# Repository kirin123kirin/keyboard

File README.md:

# 自作キーボードの沼

## 以下の要件を満たす分割キーボードがないから作りたい。

* 癖のない一般的なキーピッチ、配列である
* 日本語配列である
* 光らなくてよい
* 一般的なテンキーレスを普通に左右に分割しただけで特殊な配列ではないこと
* 「6」、「Y」、「B」は右手で押す
* IME切り替えはトグルではなくMacのように「英数」、「かな」で独立したキー切替をする
* USB Type-C
* 左右どちら側のUSBに接続しても使える
* キーキャップにかな表記はいらない
* キーキャップに英語配列時の記号も小さく表記したい
* Thinkpad トラックポイントを右手側につけたい

## 沼１：レイアウト
1. [レイアウトを考える](http://www.keyboard-layout-editor.com/)

## 沼２：回路基盤設計
2. [回路図の書き方](https://www.youtube.com/watch?v=dNfaLM5PUVM&list=PLKe0_8RR2yrSu2fZAs2D8_bfYQ3JGBO-w)
3. [自動レイアウト](https://github.com/yskoht/keyboard-layouter)
4. [自動配線](https://freerouting.mihosoft.eu/)
5. [Elecrow発注データ作成は自作](https://github.com/kirin123kirin/keyboard/blob/main/pcb/basic_L/garbar.py)

## 沼３：ファームウェア書き込み
6. [半自動firmware作成](https://kbfirmware.com/)
   -> Or import from keyboard-layout-editor.comの下のテキストボックスにKyeboard Layout Editorのraw dataの内容をコピペ

## 沼４：スイッチ選び
7. 赤軸(軽い) or 黒軸(重い) / CherryMX(90円) or KailhBox(40円)

## 沼５：キーキャップ選び
8. [Filco交換用](https://amzn.to/37BaPCG)

9. [刻印サービス](https://yushakobo.jp/keycap-laser-marking/)
  -> 高いのでやめる

## 沼６：ケース作成
10. [Plate & Case Builder](http://builder.swillkb.com/)
  -> keyboard-layout-editorのRAWデータからCADデータ自動作成

11. [Kicad PCB to Fusion360](https://garchiving.com/output-3d-model-with-kicad/)

12. [Elecrow 3D Printing Service](https://www.elecrow.com/3d-printing-service.html)

## 沼７：トラックポイントをつける
TODO

## かかった費用

| カテゴリー     	| 購入製品                                                      	| 個数  	| 単価    	| 小計(円)  	| 購入店                	|
| :---------------- | :---------------------------------------------------------------  | -------:  | --------: | --------: | :-----------------------  |
| マイコンボード 	| [Elite-C](https://yushakobo.jp/shop/elite-c/)                   	| 2     	| 2805    	| 5610     	| [遊舎工房](https://yushakobo.jp/shop/elite-c/)              	|
| マイコンボードソケット化 	| [ピンヘッダー ストリップ ピンソケット 40ピン](https://amzn.to/2Ml5kjq)                   	| 1     	| 720    	| 720     	| [Amazon](https://amzn.to/2Ml5kjq)              	|
| PCB基盤        	| 左                                                            	| 104.1 	| $27.35  	| 2,847 	| ElecrowPCB            	|
| PCB基盤        	| 右                                                            	| 104.1 	| $36.37  	| 3,786 	| ElecrowPCB            	|
| PCB基盤        	| 送料                                                          	| 104.1 	| $20.12  	| 2,094 	| ElecrowPCB            	|
| ケース         	| 左右光造形                                                      	| 104.1 	| $70     	| 7,287   	| Elecrow3DPrintService 	|
| ケース         	| トッププレート                                                	| 104.1 	| $20     	| 2,082   	| Elecrow3DPrintService 	|
| ケース         	| 送料                                                          	| 104.1 	| $14     	| 1,447  	| Elecrow3DPrintService 	|
| キースイッチ   	| [Kailh Box黒軸](https://amzn.to/3h1IFUD)                                                 	| 104.1 	| $34     	| 3508.17  	| Aliexpress            	|
| スタビライザー 	| [ブラックチェリースタビライザー](https://ja.aliexpress.com/item/32831318362.html?spm=a2g0s.9042311.0.0.46c54c4d9BF958)                                                           	| 104.1 	| $5.90   	| 614.19   	| Aliexpress            	|
| キーキャップ   	| [Majestouch 交換用キーキャップセット 日本語108キー・かななし](https://amzn.to/37BaPCG) 	| 1     	| 3420    	| 3420     	| [Amazon](https://amzn.to/37BaPCG)	|
| 配線類         	| [ダイオード500個](https://amzn.to/2Wz1wNc)                                               	| 1     	| 1082    	| 1082     	| [Amazon](https://amzn.to/2Wz1wNc)                	|
| 配線類         	| [抵抗セット](https://amzn.to/3nESg6m)                                                    	| 1     	| 890     	| 890      	| [Amazon](https://amzn.to/3nESg6m)                	|
| 配線類         	| [はんだ線](https://amzn.to/3mBjyJs)、[フラックス](https://amzn.to/3p1iNLk)                                          	| 1     	| 916     	| 916      	| [Amazon](https://amzn.to/3p1iNLk)                	|
| TRRS           	| [３．５ｍｍ４極ミニジャック　基板取付用　ＭＪ－４ＰＰ－９](https://akizukidenshi.com/catalog/g/gC-06070/)      	| 2     	| 55      	| 110      	| 秋月通商              	|
| デバック用     	| [ブレッドボード5個セット](https://amzn.to/3nD7uZn)                                       	| 1     	| 750     	| 750      	| [Amazon](https://amzn.to/3nD7uZn)                	|
| デバック用     	| [マスキングテープ3個](https://amzn.to/2J5NEa9)                                           	| 1     	| 498     	| 498      	| [Amazon](https://amzn.to/2J5NEa9)                	|
| デバック用     	| ジャンパー線、[タクトスイッチ10個](https://amzn.to/3mDJrrU)                              	| 1     	| 660     	| 660      	| 秋月通商,[Amazon](https://amzn.to/3mDJrrU)              	|
| 工具           	| [はんだキット](https://amzn.to/2WwUdWA)                                                  	| 1     	| 3599    	| 3599     	| [Amazon](https://amzn.to/2WwUdWA)                	|
| 工具           	| [ノギス](https://amzn.to/3mIHx9L)                                	| 1     	| 799    	| 799     	| [Amazon](https://amzn.to/3mIHx9L)	|
| レイアウト設計        	| [キーボードレイアウト設計](http://www.keyboard-layout-editor.com/)                                                         	| 1     	| 0       	| 0        	| OSS             	|
| PCB設計        	| [Kicad](https://kicad.org/)                                                         	| 1     	| 0       	| 0        	| OSS             	|
| PCB設計        	| [基盤自動レイアウトプラグイン](https://github.com/yskoht/keyboard-layouter)                                                         	| 1     	| 0       	| 0        	| OSS             	|
| PCB設計        	| [freerouting(基盤自動配線)](https://github.com/freerouting/freerouting)                                                         	| 1     	| 0       	| 0        	| OSS             	|
| ケース、トッププレート設計     	| [Fusion360個人利用](https://www.autodesk.co.jp/products/fusion-360/overview)                                                 	| 1     	| 0       	| 0        	| Adobe                 	|
| Firmware       	| [qmk_firmware](https://github.com/qmk/qmk_firmware)                                                  	| 1     	| 0       	| 0        	| Github                	|
| Firmware       	| [Keyboard Firmware Builder](https://kbfirmware.com/)                                                         	| 1     	| 0       	| 0        	| OSS             	|
| Firmwareビルド用 	| [Ubuntu18.04LTS Server](http://ftp.riken.jp/Linux/ubuntu-releases/18.04/)                                                	| 1     	| 0       	| 0        	| Ubuntu                	|
| Firmwareソース編集用	| [Visual Studio2019Comunity](https://visualstudio.microsoft.com/ja/downloads/)                                   	| 1     	| 0       	| 0        	| MicroSoft             	|
|                	|                                                               	|       	| 合計    	| 42,334円	|

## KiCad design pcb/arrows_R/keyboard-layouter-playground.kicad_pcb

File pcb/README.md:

** qmk data version rev1 later **

# 自作基盤設計データ
## Lisense
This software is released under the [Creative Commons CC-BY-SA 4.0 License](https://creativecommons.org/licenses/by-sa/4.0/legalcode), see LICENSE.

## [Powerd by Kicad](https://kicad.org/)

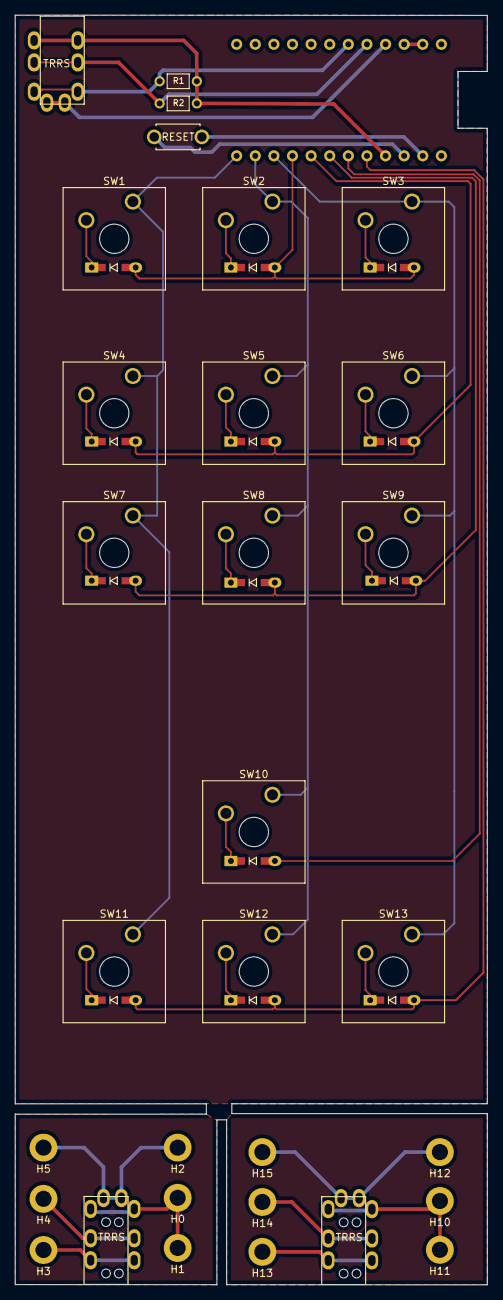
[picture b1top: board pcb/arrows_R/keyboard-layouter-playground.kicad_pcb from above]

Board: 2 copper layers, 64.4 x 173.3 mm, 45 parts (1 on the bottom side), 36 nets.

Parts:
D1, D2, D3, D4, D5, D6, D7, D8, D9, D10, D11, D12, D13: DIODE; D3_TH
H0, H10: MIC-Left; MountingHole_2.2mm_M2_ISO14580_Pad
H1, H11: MIC-Right; MountingHole_2.2mm_M2_ISO14580_Pad
H2, H5, H12, H15: GND; MountingHole_2.2mm_M2_ISO14580_Pad
H3, H13: Left; MountingHole_2.2mm_M2_ISO14580_Pad
H4, H14: Right; MountingHole_2.2mm_M2_ISO14580_Pad
J1, J2, J3: MJ-4PP-9
R1, R2: 4.7k; R
SW1, SW2, SW3, SW4, SW5, SW6, SW7, SW8, SW9, SW10, SW11, SW12, SW13: SW_Push; SW_Cherry_MX_1.00u_Plate
SW_RST2: SW_PUSH; ResetSW
U1: ProMicro; ProMicro_v3.5

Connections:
COL1: SW1.1, SW4.1, SW7.1, SW11.1, U1.13
COL2: SW2.1, SW5.1, SW8.1, SW10.1, SW12.1, U1.14
COL3: SW3.1, SW6.1, SW9.1, SW13.1, U1.15
unnamed: D1.1, SW1.2
unnamed: D2.1, SW2.2
unnamed: D3.1, SW3.2
unnamed: D4.1, SW4.2
unnamed: D5.1, SW5.2
unnamed: D6.1, SW6.2
unnamed: D7.1, SW7.2
unnamed: D8.1, SW8.2
unnamed: D9.1, SW9.2
unnamed: D10.1, SW10.2
unnamed: D11.1, SW11.2
unnamed: D12.1, SW12.2
unnamed: D13.1, SW13.2
unnamed: H0.1, H1.1, J1.D
unnamed: H2.1, H5.1, J1.A
unnamed: H3.1, J1.B
unnamed: H4.1, J1.C
unnamed: H10.1, H11.1, J3.D
unnamed: H12.1, H15.1, J3.A
unnamed: H13.1, J3.B
unnamed: H14.1, J3.C
unnamed: J2.A, U1.4
unnamed: J2.B, R1.2, R2.2, U1.21
unnamed: J2.D, R1.1, U1.6
unnamed: SW_RST2.1, U1.22
unnamed: SW_RST2.2, U1.23
unnamed: U1.2, U1.3
SDA2: J2.C, R2.1, U1.5
row1: D1.2, D2.2, D3.2, U1.16
row2: D4.2, D5.2, D6.2, U1.17
row3: D7.2, D8.2, D9.2, U1.18
row4: D10.2, U1.19
row5: D11.2, D12.2, D13.2, U1.20

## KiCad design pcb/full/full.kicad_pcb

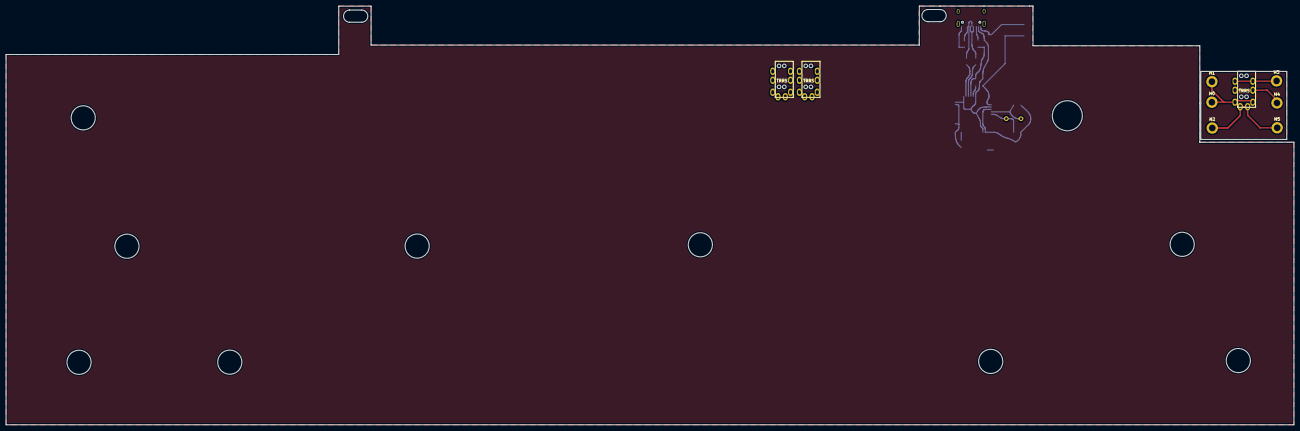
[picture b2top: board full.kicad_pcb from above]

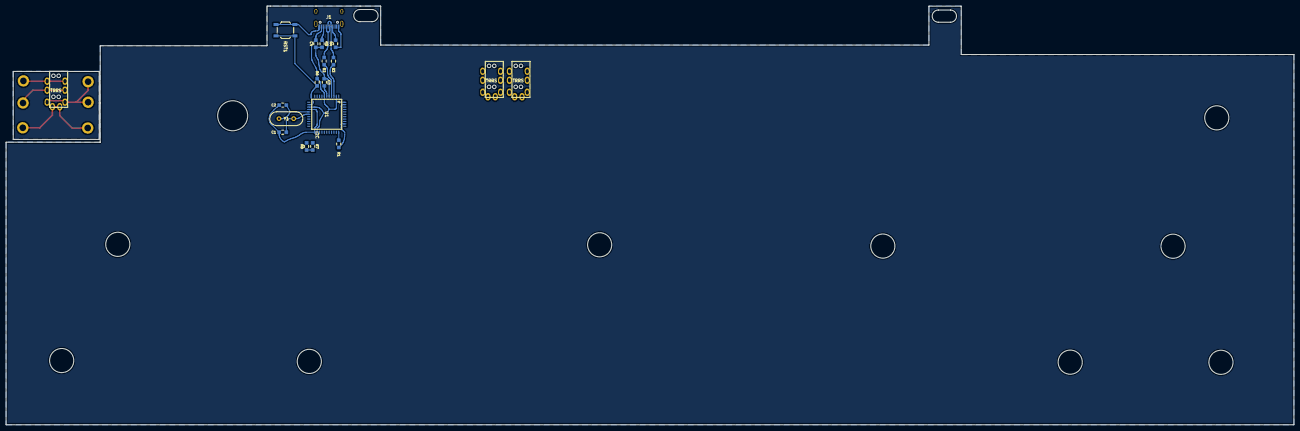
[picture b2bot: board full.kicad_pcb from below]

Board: 2 copper layers, 429.5 x 139.6 mm, 25 parts (15 on the bottom side), 15 nets.

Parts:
C1, C2: 22p; 2012M
C3, C4: 1u; 2012M
H0: MIC-Left; MountingHole_2.2mm_M2_ISO14580_Pad
H1: MIC-Right; MountingHole_2.2mm_M2_ISO14580_Pad
H2, H5: GND; MountingHole_2.2mm_M2_ISO14580_Pad
H3: Left; MountingHole_2.2mm_M2_ISO14580_Pad
H4: Right; MountingHole_2.2mm_M2_ISO14580_Pad
J1: MJ-4PP-9
J1#2: TYPE-C-31-M-12
J2, J3: AudioJack4; MJ-4PP-9
R1, R6: 10k; 2012M
R2, R3: 22; 2012M
R4, R5, R7, R8: 5.1k; 2012M
RST1: SW_Push; SW_SPST_TL3342
U1: ATmega32U4-AU; TQFP44
Y1: 16MHz; Crystal-HC-49-S

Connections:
D+: R2.1, U1.4
D-: R3.1, U1.3
GND: C1.2, C2.2, C3.2, C4.2, J1#2.A1B12, J1#2.B1A12, R1.1, R4.1, R5.1, RST1.1, U1.5, U1.15, U1.23, U1.35, U1.43
unnamed: C1.1, U1.17, Y1.1
unnamed: C2.1, U1.16, Y1.2
unnamed: C3.1, U1.6
unnamed: J1#2.A5, R4.2
unnamed: J1#2.A6, J1#2.B6, R2.2
unnamed: J1#2.A7, J1#2.B7, R3.2
unnamed: J1#2.B5, R5.2
unnamed: R1.2, U1.33
RESET: R6.1, RST1.2, U1.13
SCL: R7.1, U1.18
SDA: R8.1, U1.19
VCC: C4.1, J1#2.A4B9, J1#2.B4A9, R6.2, R7.2, R8.2, U1.2, U1.7, U1.14, U1.24, U1.34, U1.44

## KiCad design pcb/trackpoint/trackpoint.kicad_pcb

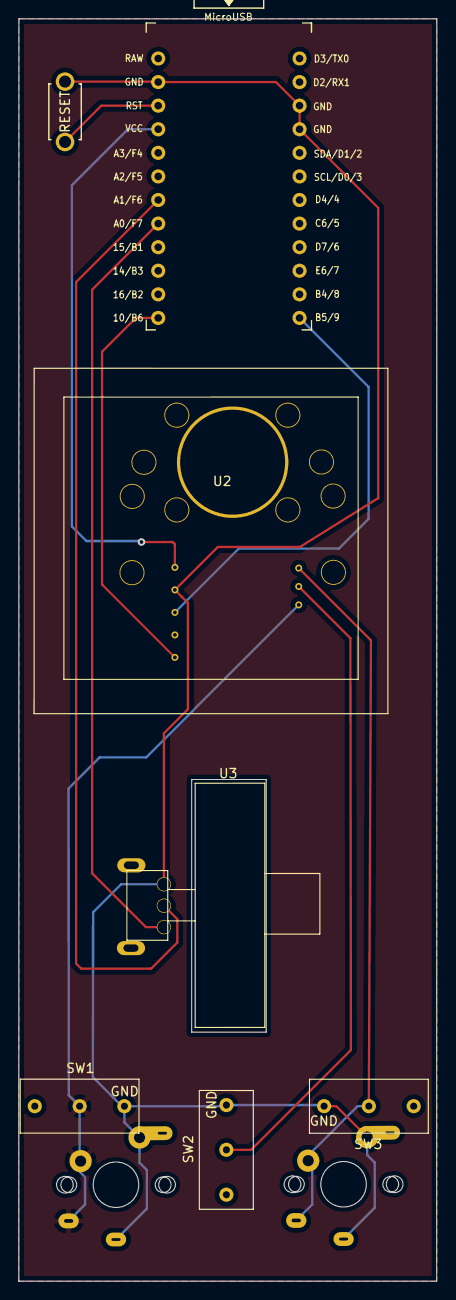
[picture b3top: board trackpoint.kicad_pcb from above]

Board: 2 copper layers, 45.0 x 135.9 mm, 9 parts (0 on the bottom side), 10 nets.

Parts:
SW0: SW_RESET; ResetSW
SW01, SW03: SW_Push; CherryMX_ChocV2_1u
SW1, SW2, SW3: MouseClick; mouse_click
U1: ProMicro; ProMicro_v3.5
U2: trackpoint_R61
U3: mouse_wheel

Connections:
CLK: U1.12, U2.6
DATA: U1.13, U2.1
GND: SW0.2, SW01.2, SW1.2, SW2.2, SW03.2, SW3.2, U1.3, U1.4, U1.23, U2.7, U3.1
unnamed: SW0.1, U1.22
unnamed: SW01.1, SW1.1, U2.3
unnamed: SW2.1, U2.4
unnamed: SW03.1, SW3.1, U2.5
unnamed: U1.17, U3.3
unnamed: U1.18, U3.2
VCC: U1.21, U2.8

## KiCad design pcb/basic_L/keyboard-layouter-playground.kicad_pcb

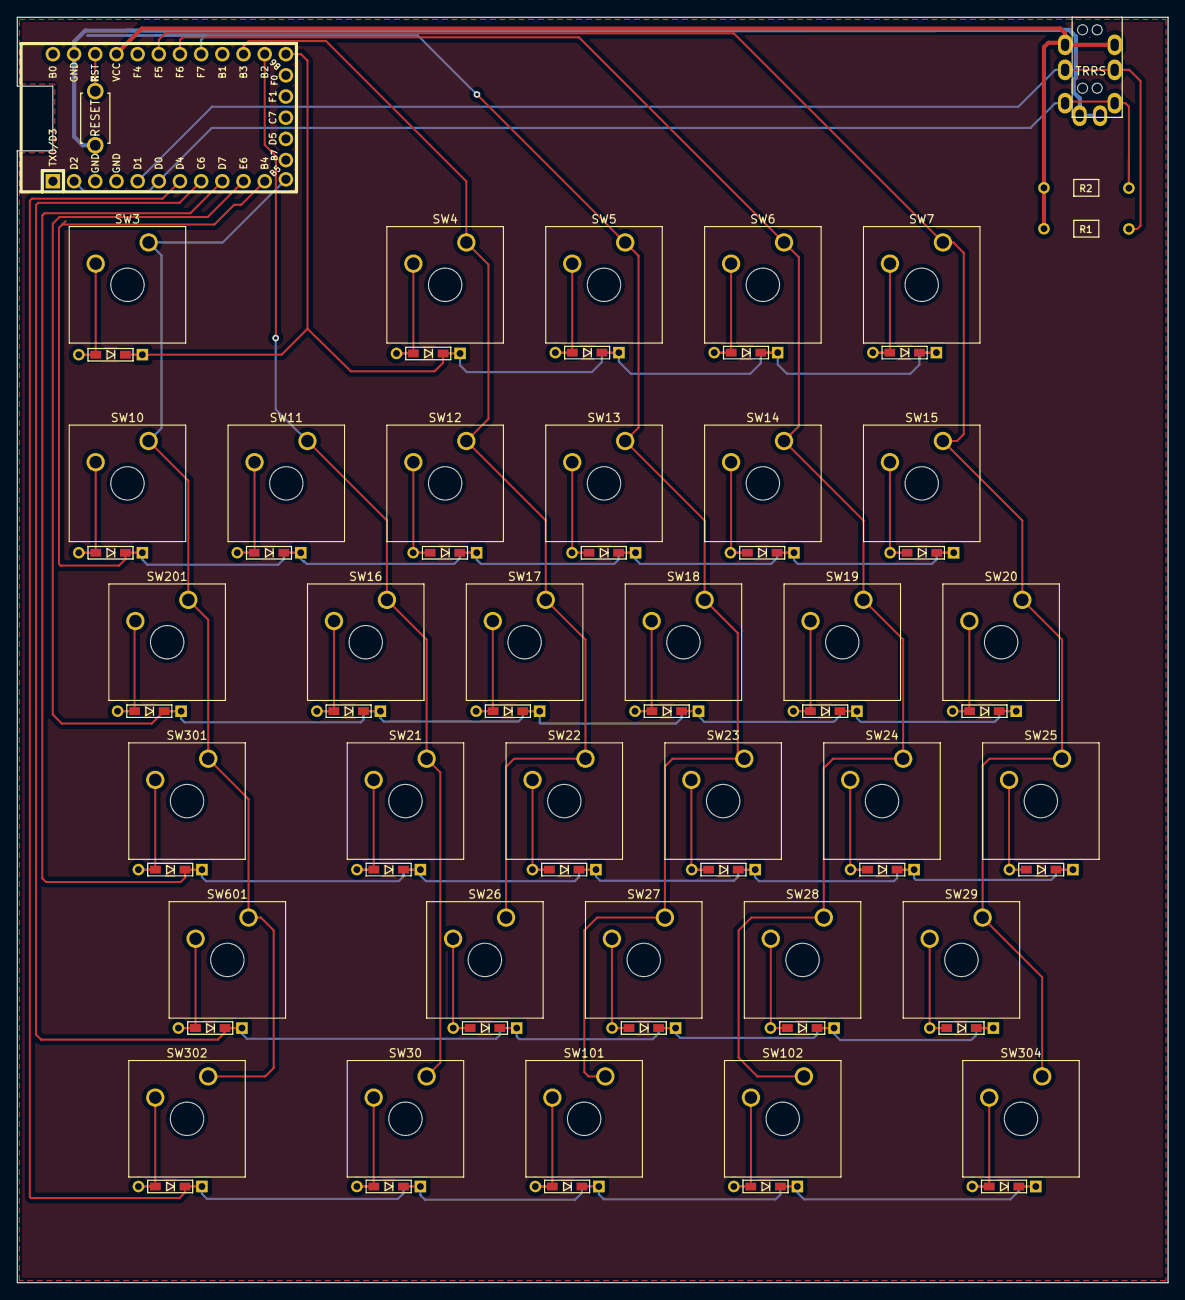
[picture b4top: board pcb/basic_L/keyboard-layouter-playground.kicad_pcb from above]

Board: 2 copper layers, 138.0 x 151.8 mm, 71 parts (0 on the bottom side), 50 nets.

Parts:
D3, D4, D5, D6, D7, D10, D11, D12, D13, D14, D15, D16, D17, D18, D19, D20, D21, D22, D23, D24, D25, D26, D27, D28, D29, D30, D101, D102, D201, D301, D302, D304, D601: DIODE; D3_TH_SMD_Horizontal
J1: MJ-4PP-9
R1, R2: 4.7k; R
SW3, SW4, SW5, SW6, SW7, SW10, SW11, SW12, SW13, SW14, SW15, SW16, SW17, SW18, SW19, SW20, SW21, SW22, SW23, SW24, SW25, SW26, SW27, SW28, SW29, SW30: SW_Push; SW_Cherry_MX_1.00u_Plate
SW101, SW102: SW_Push; SW_Cherry_MX_1.25u_Plate
SW201: SW_Push; SW_Cherry_MX_1.50u_Plate
SW301, SW302, SW304: SW_Push; SW_Cherry_MX_1.75u_Plate
SW601: SW_Push; SW_Cherry_MX_2.25u_Plate
SW_RST1: SW_PUSH; ResetSW
U1: Elite-C-keebio; Elite-C

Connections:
COL0: SW3.1, SW10.1, SW201.1, SW301.1, SW302.1, SW601.1, U1.12
COL1: SW11.1, SW16.1, SW21.1, SW30.1, U1.14
COL2: SW4.1, SW12.1, SW17.1, SW22.1, SW26.1, U1.15
COL3: SW5.1, SW13.1, SW18.1, SW23.1, SW27.1, SW101.1, U1.17
COL4: SW6.1, SW14.1, SW19.1, SW24.1, SW28.1, SW102.1, U1.18
COL5: SW7.1, SW15.1, SW20.1, SW25.1, SW29.1, SW304.1, U1.19
GND: J1.A, SW_RST1.2, U1.23
unnamed: D3.1, SW3.2
unnamed: D4.1, SW4.2
unnamed: D5.1, SW5.2
unnamed: D6.1, SW6.2
unnamed: D7.1, SW7.2
unnamed: D10.1, SW10.2
unnamed: D11.1, SW11.2
unnamed: D12.1, SW12.2
unnamed: D13.1, SW13.2
unnamed: D14.1, SW14.2
unnamed: D15.1, SW15.2
unnamed: D16.1, SW16.2
unnamed: D17.1, SW17.2
unnamed: D18.1, SW18.2
unnamed: D19.1, SW19.2
unnamed: D20.1, SW20.2
unnamed: D21.1, SW21.2
unnamed: D22.1, SW22.2
unnamed: D23.1, SW23.2
unnamed: D24.1, SW24.2
unnamed: D25.1, SW25.2
unnamed: D26.1, SW26.2
unnamed: D27.1, SW27.2
unnamed: D28.1, SW28.2
unnamed: D29.1, SW29.2
unnamed: D30.1, SW30.2
unnamed: D101.1, SW101.2
unnamed: D102.1, SW102.2
unnamed: D201.1, SW201.2
unnamed: D301.1, SW301.2
unnamed: D302.1, SW302.2
unnamed: D304.1, SW304.2
unnamed: D601.1, SW601.2
unnamed: J1.D, R2.1, U1.2, U1.6
unnamed: SW_RST1.1, U1.22
SDA1: J1.C, R1.1, U1.5
VCC: J1.B, R1.2, R2.2, U1.21
row1: D3.2, D4.2, D5.2, D6.2, D7.2, U1.13
row2: D10.2, D11.2, D12.2, D13.2, D14.2, D15.2, U1.11
row3: D16.2, D17.2, D18.2, D19.2, D20.2, D201.2, U1.10
row4: D21.2, D22.2, D23.2, D24.2, D25.2, D301.2, U1.9
row5: D26.2, D27.2, D28.2, D29.2, D601.2, U1.8
row6: D30.2, D101.2, D102.2, D302.2, D304.2, U1.7

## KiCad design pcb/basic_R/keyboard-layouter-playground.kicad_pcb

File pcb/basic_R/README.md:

Powered by [Keyboard Layouter](https://github.com/yskoht/keyboard-layouter) plugin.

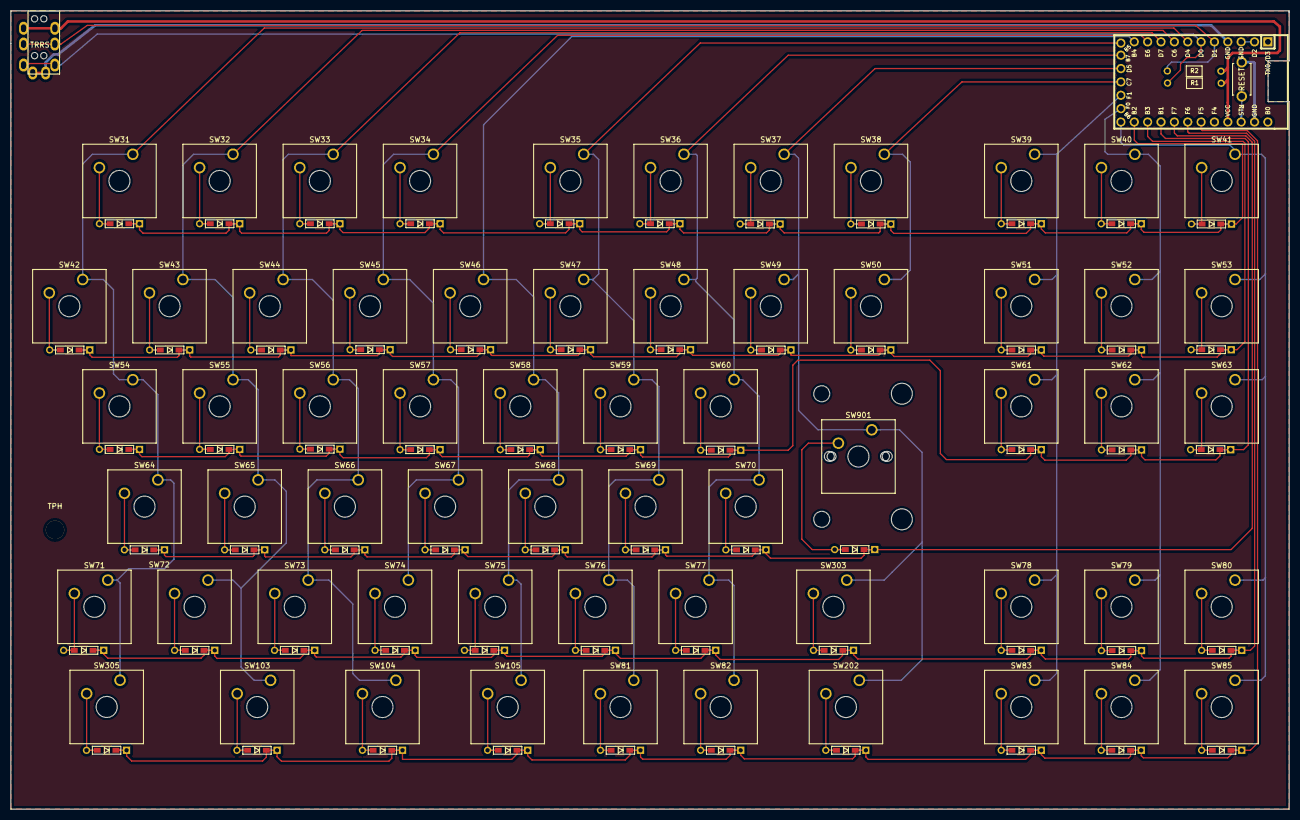
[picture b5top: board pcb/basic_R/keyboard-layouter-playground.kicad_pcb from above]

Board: 2 copper layers, 243.0 x 151.8 mm, 130 parts (0 on the bottom side), 87 nets.

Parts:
D31, D32, D33, D34, D35, D36, D37, D38, D39, D40, D41, D42, D43, D44, D45, D46, D47, D48, D49, D50, D51, D52, D53, D54, D55, D56, D57, D58, D59, D60, D61, D62, D63, D64, D65, D66, D67, D68, D69, D70, D71, D72, D73, D74, D75, D76, D77, D78, D79, D80, D81, D82, D83, D84, D85, D103, D104, D105, D202, D303, D305, D901: DIODE; D3_TH_SMD_Horizontal
J2: MJ-4PP-9
R1, R2: 4.7k; R
SW31, SW32, SW33, SW34, SW35, SW36, SW37, SW38, SW39, SW40, SW41, SW42, SW43, SW44, SW45, SW46, SW47, SW48, SW49, SW50, SW51, SW52, SW53, SW54, SW55, SW56, SW57, SW58, SW59, SW60, SW61, SW62, SW63, SW64, SW65, SW66, SW67, SW68, SW69, SW70, SW71, SW72, SW73, SW74, SW75, SW76, SW77, SW78, SW79, SW80, SW81, SW82, SW83, SW84, SW85: SW_Push; SW_Cherry_MX_1.00u_Plate
SW103, SW104, SW105: SW_Push; SW_Cherry_MX_1.25u_Plate
SW202: SW_Push; SW_Cherry_MX_1.50u_Plate
SW303, SW305: SW_Push; SW_Cherry_MX_1.75u_Plate
SW901: SW_Push; SW_Cherry_MX_ISOEnter_Stabilizer_5pin
SW_RST2: SW_PUSH; ResetSW
TPH: MountingHole_3.5mm
U2: Elite-C

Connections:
COL9: SW31.1, SW42.1, SW54.1, SW64.1, SW71.1, SW305.1, U2.7
COL10: SW32.1, SW43.1, SW55.1, SW65.1, SW72.1, SW103.1, U2.8
COL11: SW33.1, SW44.1, SW56.1, SW66.1, SW73.1, SW104.1, U2.9
COL12: SW34.1, SW45.1, SW57.1, SW67.1, SW74.1, U2.10
COL13: SW46.1, SW58.1, SW68.1, SW75.1, SW105.1, U2.11
COL14: SW35.1, SW47.1, SW59.1, SW69.1, SW76.1, SW81.1, U2.12
COL15: SW36.1, SW48.1, SW60.1, SW70.1, SW77.1, SW82.1, U2.25
COL16: SW37.1, SW49.1, SW202.1, SW303.1, SW901.1, U2.26
COL17: SW38.1, SW50.1, U2.27
COL18: SW39.1, SW51.1, SW61.1, SW78.1, SW83.1, U2.28
COL19: SW40.1, SW52.1, SW62.1, SW79.1, SW84.1, U2.29
COL20: SW41.1, SW53.1, SW63.1, SW80.1, SW85.1, U2.13
unnamed: D31.1, SW31.2
unnamed: D32.1, SW32.2
unnamed: D33.1, SW33.2
unnamed: D34.1, SW34.2
unnamed: D35.1, SW35.2
unnamed: D36.1, SW36.2
unnamed: D37.1, SW37.2
unnamed: D38.1, SW38.2
unnamed: D39.1, SW39.2
unnamed: D40.1, SW40.2
unnamed: D41.1, SW41.2
unnamed: D42.1, SW42.2
unnamed: D43.1, SW43.2
unnamed: D44.1, SW44.2
unnamed: D45.1, SW45.2
unnamed: D46.1, SW46.2
unnamed: D47.1, SW47.2
unnamed: D48.1, SW48.2
unnamed: D49.1, SW49.2
unnamed: D50.1, SW50.2
unnamed: D51.1, SW51.2
unnamed: D52.1, SW52.2
unnamed: D53.1, SW53.2
unnamed: D54.1, SW54.2
unnamed: D55.1, SW55.2
unnamed: D56.1, SW56.2
unnamed: D57.1, SW57.2
unnamed: D58.1, SW58.2
unnamed: D59.1, SW59.2
unnamed: D60.1, SW60.2
unnamed: D61.1, SW61.2
unnamed: D62.1, SW62.2
unnamed: D63.1, SW63.2
unnamed: D64.1, SW64.2
unnamed: D65.1, SW65.2
unnamed: D66.1, SW66.2
unnamed: D67.1, SW67.2
unnamed: D68.1, SW68.2
unnamed: D69.1, SW69.2
unnamed: D70.1, SW70.2
unnamed: D71.1, SW71.2
unnamed: D72.1, SW72.2
unnamed: D73.1, SW73.2
unnamed: D74.1, SW74.2
unnamed: D75.1, SW75.2
unnamed: D76.1, SW76.2
unnamed: D77.1, SW77.2
unnamed: D78.1, SW78.2
unnamed: D79.1, SW79.2
unnamed: D80.1, SW80.2
unnamed: D81.1, SW81.2
unnamed: D82.1, SW82.2
unnamed: D83.1, SW83.2
unnamed: D84.1, SW84.2
unnamed: D85.1, SW85.2
unnamed: D103.1, SW103.2
unnamed: D104.1, SW104.2
unnamed: D105.1, SW105.2
unnamed: D202.1, SW202.2
unnamed: D303.1, SW303.2
unnamed: D305.1, SW305.2
unnamed: D901.1, SW901.2
unnamed: J2.A, U2.4
unnamed: J2.B, R1.2, R2.2, U2.21
unnamed: J2.D, R1.1, U2.6
unnamed: SW_RST2.1, U2.22
unnamed: SW_RST2.2, U2.23
unnamed: U2.2, U2.3
SDA2: J2.C, R2.1, U2.5
row7: D31.2, D32.2, D33.2, D34.2, D35.2, D36.2, D37.2, D38.2, D39.2, D40.2, D41.2, U2.14
row8: D42.2, D43.2, D44.2, D45.2, D46.2, D47.2, D48.2, D49.2, D50.2, D51.2, D52.2, D53.2, U2.15
row9: D54.2, D55.2, D56.2, D57.2, D58.2, D59.2, D60.2, D61.2, D62.2, D63.2, U2.16
row10: D64.2, D65.2, D66.2, D67.2, D68.2, D69.2, D70.2, D901.2, U2.17
row11: D71.2, D72.2, D73.2, D74.2, D75.2, D76.2, D77.2, D78.2, D79.2, D80.2, D303.2, U2.18
row12: D81.2, D82.2, D83.2, D84.2, D85.2, D103.2, D104.2, D105.2, D202.2, D305.2, U2.19

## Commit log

2020-12-08 readme edit
2020-12-08 bugfix
2020-12-08 upload png
2020-12-08 refer
2020-12-08 手順メモ
2020-12-09 case build
2020-12-12 case data make
2020-12-13 bugfix. and PCB Data Elecrow ordered
2020-12-13 add cost
2020-12-15 case closed edited.
2020-12-25 pcb bugfix trrs hole add
2020-12-27 left promicro both OK.
2020-12-27 bugfix. need files
2020-12-29 redesigned.
2020-12-29 case update.
2020-12-29 fuyou
2020-12-30 cost updated
2020-12-30 readme update
2021-01-11 stable. bugfixed
2021-01-18 library add 5pin and Stabilizer
2021-02-05 bugfix datasheet add
2021-02-05 padd
2021-12-20 keyboard settings and added arrows_R
2021-12-20 miss
